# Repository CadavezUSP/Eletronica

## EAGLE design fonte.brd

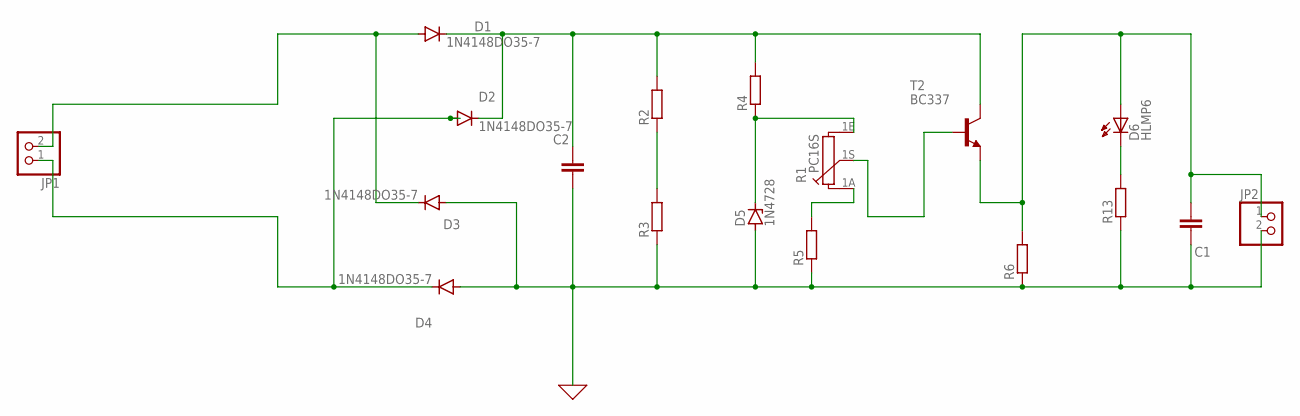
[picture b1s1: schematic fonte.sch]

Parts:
C1, C2: C5/3; C5B3
D1, D2, D3, D4: 1N4148DO35-7; DO35-7
D5: 1N4728; DO41Z10
D6: HLMP6
JP1, JP2: PINHD-1X2; 1X02
R1: PC16S
R2, R3, R4, R5, R6, R13: R-EU_0204/7; 0204/7
T2: BC337; TO92

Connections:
0: C1.1, C2.2, D3.A, D4.A, D5.A, JP2.2, R3.1, R5.1, R6.1, R13.1
1: C1.2, D6.A, JP2.1, R6.2, T2.1 (E)
unnamed: R2.1, R3.2
unnamed: D1.A, D3.C, JP1.2
unnamed: R1.1A, R5.2
unnamed: D2.A, D4.C, JP1.1
unnamed: D5.C, R1.1E, R4.1
unnamed: R1.1S, T2.2 (B)
unnamed: D6.K, R13.2
unnamed: C2.1, D1.C, D2.C, R2.2, R4.2, T2.3 (C)

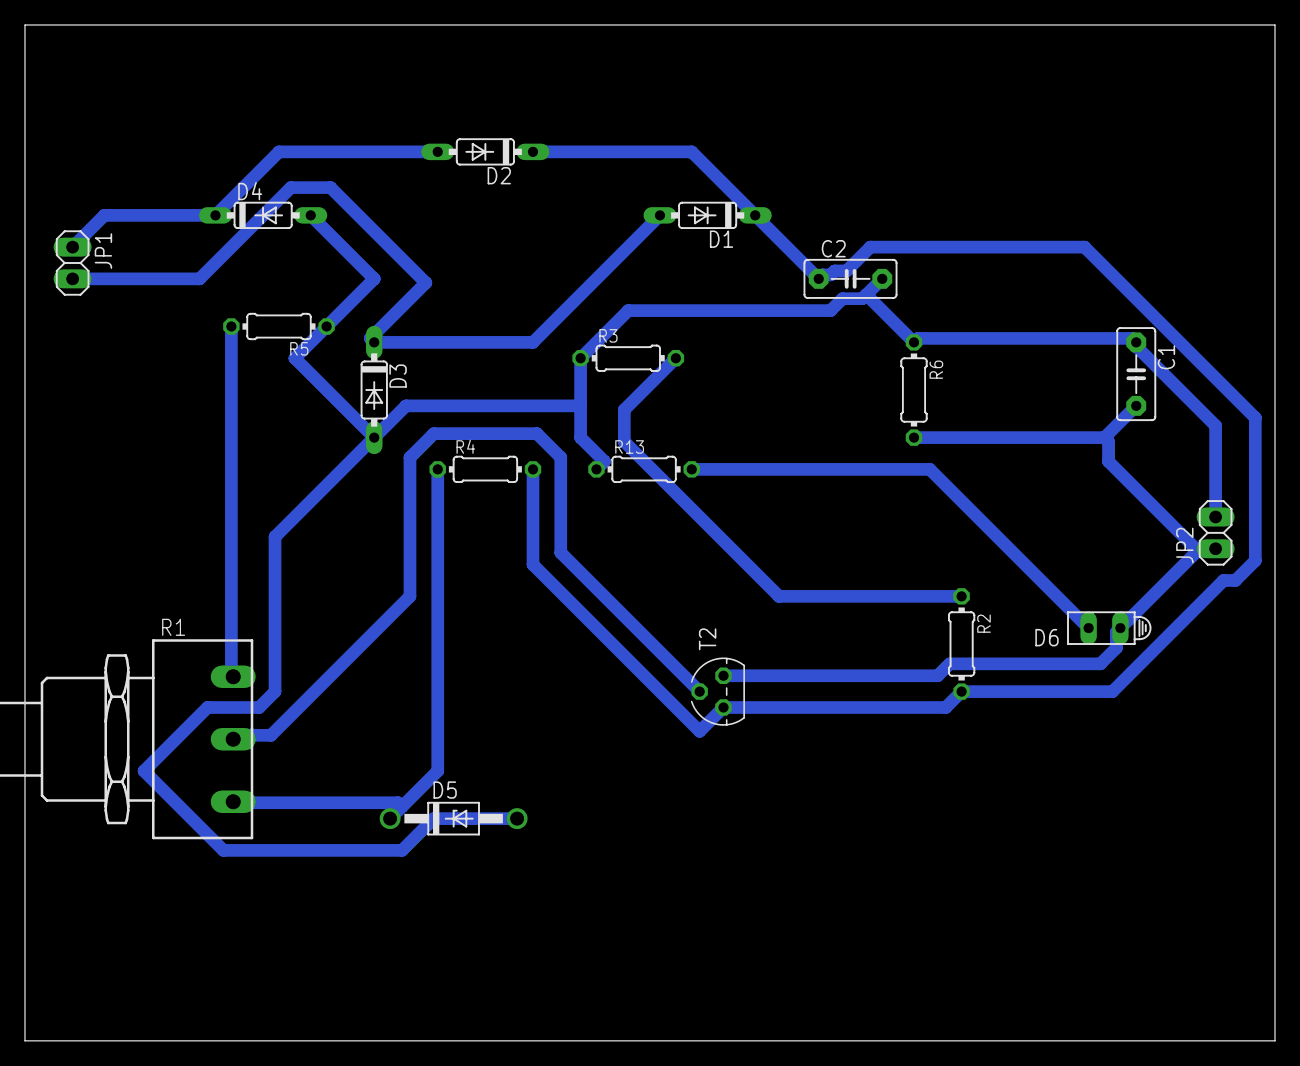
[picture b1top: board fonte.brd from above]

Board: 2 copper layers, 100.0 x 81.3 mm, 18 parts (0 on the bottom side), 10 nets.
